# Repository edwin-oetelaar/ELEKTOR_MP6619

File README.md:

# ELEKTOR_MP6619 Breakout Board Project

This repository contains the KiCAD project files for the Elektor Magazine article about the MP6619 H-bridge chip Breakout Board.

## Software Requirement

This project was designed using the latest nightly version of KiCAD. 

### Installation on Ubuntu:

To install the nightly build of KiCAD on Ubuntu, you can use the following commands:

```bash
sudo add-apt-repository ppa:kicad/kicad-dev-nightly
sudo apt update
sudo apt install kicad-nightly
```
### Installation on Windows:
The KiCAD files have also been tested on Windows. To download the nightly builds for Windows, please visit this link. https://downloads.kicad.org/kicad/windows/explore/nightlies

### Project History
The project evolved over time:

* **First Attempt (Dual Chip Breakout Board)**: The initial design of the project was a dual chip breakout board, found in the directory 2HBR_NG.

* **Second Attempt (Single Chip Breakout Board)**: The design was later revised to create a single chip breakout board, found in the directory 2HBR_NG/2HBR_MINIMAL.

To open the project, use the following command in terminal:

```console
user@werkpc:~$ kicad-nightly 2HBR_NG/2HBR_MINIMAL/2HBR_MINIMAL.kicad_pro
```
### Output Files
The 'out1' directory contains the Gerber files used to manufacture the PCB board.

### Support
If you encounter any issues or require further assistance, feel free to create an issue in this repository.

### License
MIT license, no warranties.
The MIT license is a permissive license that is short and easy to understand. It permits users to use, copy, modify, merge, publish, distribute, sublicense, and sell the software and associated documentation files. Here's the general summary:

  * Use: You can use the hardware in any setting, for any purpose, and without needing to pay for it.

  * Copy: You can make as many copies of the hardware as you want, and give them away or sell them.
  * Modify: You can make changes to the hardware, and use the modified hardware. You can also distribute modified copies, or sell hardware based on the modified designs.
  * Merge: You can combine the hardware with other hardware to make something new, and distribute or sell that.
  * Publish: You can share copies of the hardware, or make them publicly available (for example, by posting them online).
  * Distribute: You can give copies of the hardware to other people.
  * Sublicense: You can allow other people to do any of the above with the hardware.
  * Sell: You can sell copies of the hardware.

The above permissions are granted for free, and apply to both the original version of the hardware and to any modified versions that you make.

The license also includes a "disclaimer of warranty" stating that the hardware is provided "as is" without warranty of any kind.

However, please note that any derivative work you create must maintain the original licensing, i.e., the licensing information must always be included in the hardware documentation, design files, etc.

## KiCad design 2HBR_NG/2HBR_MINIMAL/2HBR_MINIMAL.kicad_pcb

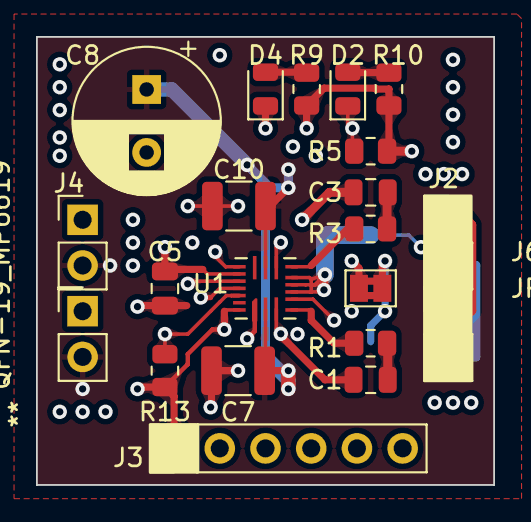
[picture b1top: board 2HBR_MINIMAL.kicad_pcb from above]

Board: 4 copper layers, 25.4 x 24.9 mm, 22 parts (1 on the bottom side), 18 nets.

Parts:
C1, C3: 100 nF / 50V; C_0805_2012Metric
C5: 1uF/50V; C_0805_2012Metric
C7, C10: 4u7 1210; C_1210_3225Metric
C8: 120uF/35; CP_Radial_D8.0mm_P3.50mm
D2: LED RED 0805; LED_0805_2012Metric
D4: LED GREEN 0805; LED_0805_2012Metric
J2, J4, J5, J6: Screw_Terminal_01x02; PinHeader_1x02_P2.54mm_Vertical
J3: Conn_01x06; PinHeader_1x06_P2.54mm_Vertical
JP1: Jumper_2_Bridged; SolderJumper-2_P1.3mm_Bridged2Bar_Pad1.0x1.5mm
R1, R3: 10 R; R_0805_2012Metric
R5: 100k; R_0805_2012Metric
R8: 0.05R SENSE; R_2512_6332Metric
R9: 1K0 0603; R_0805_2012Metric
R10: 1K0 0805; R_0805_2012Metric
R13: 80k 0805; R_0805_2012Metric
U1: QFN-19_MP6619; MP6619GQ-P

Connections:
GND: C7.2, C8.2, C10.2, J4.1, J5.1, JP1.2 (B), R8.2
GNDA: C5.1, D4.1 (K), J3.1, JP1.1 (A), R13.2, U1.19 (AGND)
unnamed: C1.2, R1.2
unnamed: C3.1, R3.1
unnamed: D2.2 (A), R10.2
unnamed: D4.2 (A), R9.2
unnamed: R3.2, U1.9 (BST1)
unnamed: R1.1, U1.4 (BST2)
U1-EN: J3.4, U1.5 (EN)
U1-IFB: R8.1, U1.1 (IFB), U1.6 (LSS), U1.7 (LSS), U1.8 (LSS)
U1-IN1: J3.3, U1.15 (IN1)
U1-IN2: J3.2, U1.16 (IN2)
U1-ISET: R13.1, U1.17 (ISET)
U1-OUT1: C3.2, J2.1, J6.1, U1.10 (OUT1)
U1-OUT2: C1.1, J2.2, J6.2, U1.3 (OUT2)
U1-VCC: C5.2, J3.6, R5.1, R9.1, R10.1, U1.14 (VCC)
U1-nFault: D2.1 (K), J3.5, R5.2, U1.13 (NFAULT)
VIN: C7.1, C8.1, C10.1, J4.2, J5.2, U1.2 (VIN), U1.11 (VIN)

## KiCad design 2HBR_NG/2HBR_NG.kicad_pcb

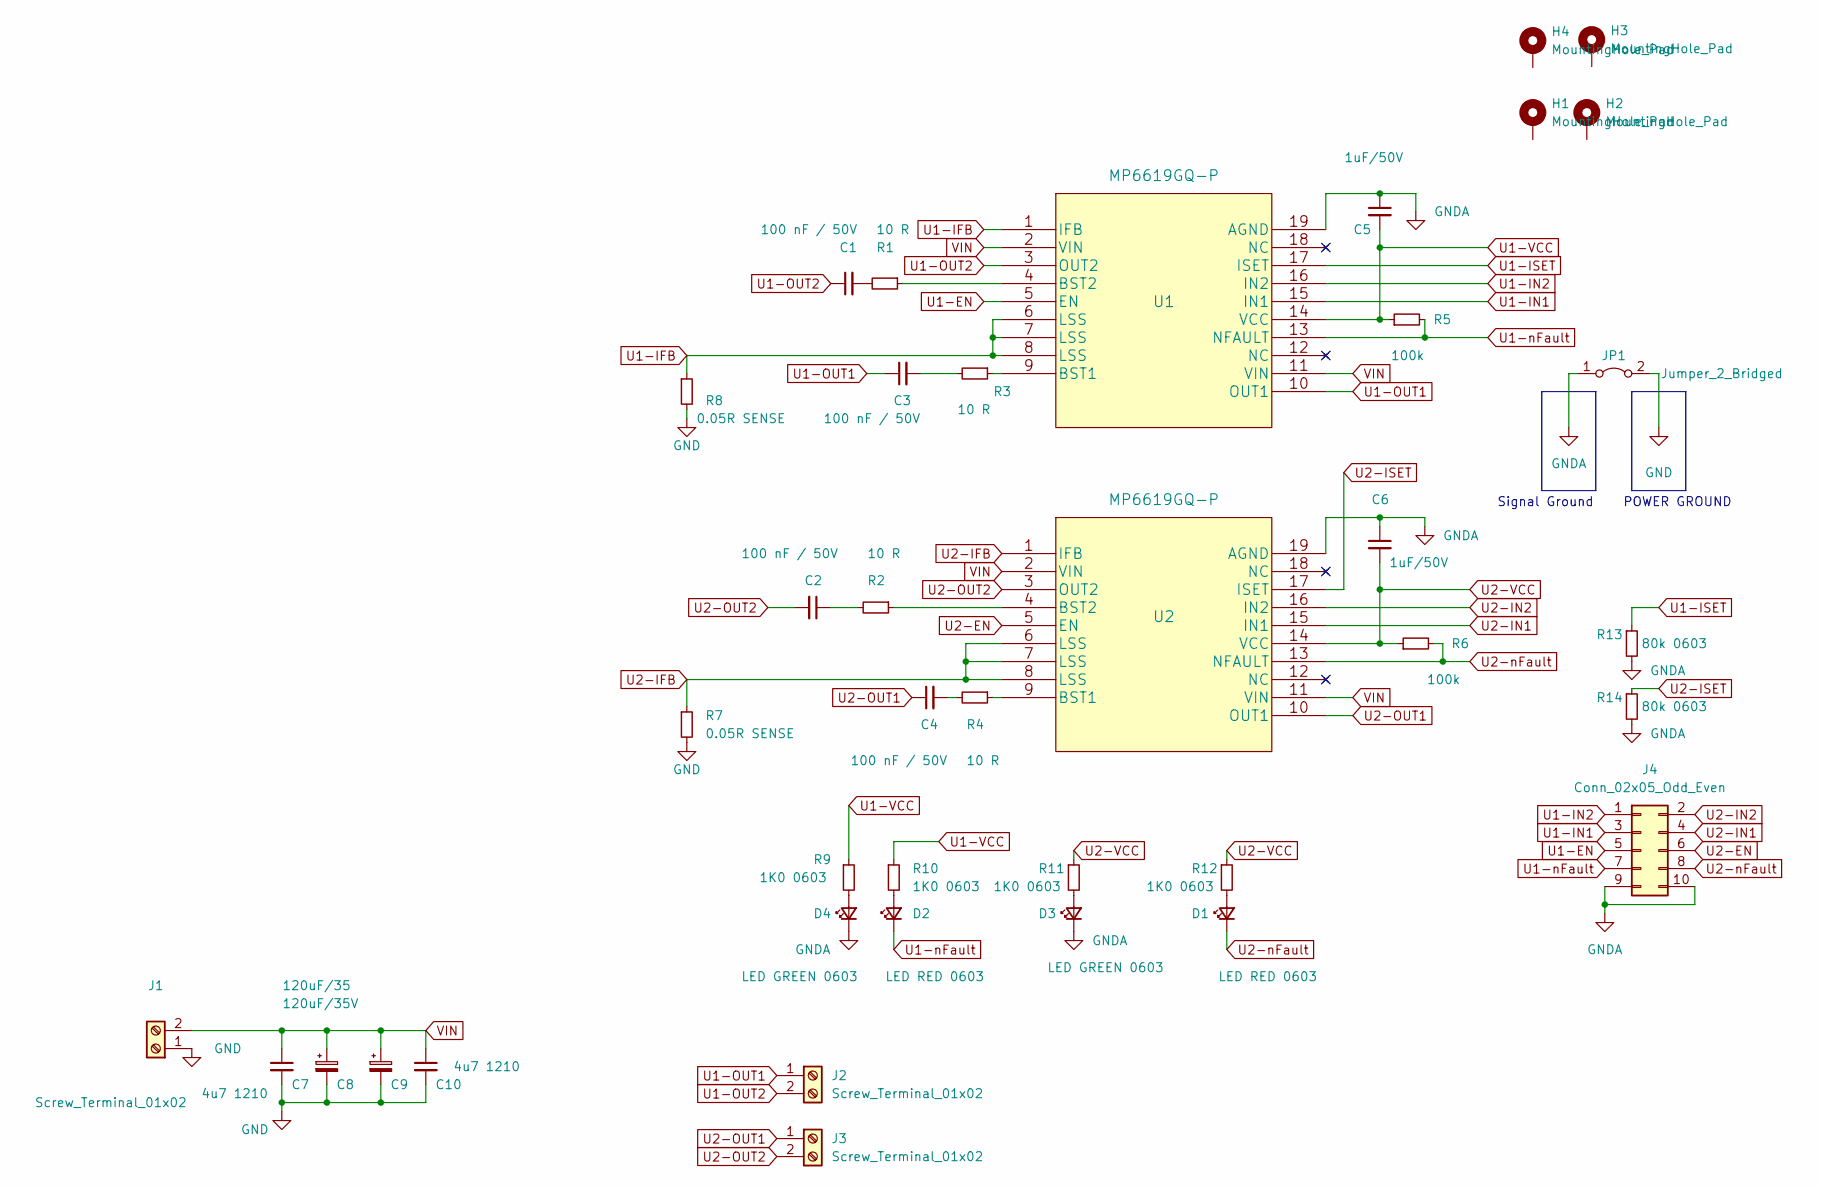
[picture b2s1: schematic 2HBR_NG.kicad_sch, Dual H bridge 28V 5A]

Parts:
C1, C2, C3, C4: 100 nF / 50V; C_0805_2012Metric; PARTNO MC0805B104K500CT
C5, C6: 1uF/50V; C_0805_2012Metric
C7, C10: 4u7 1210; C_1210_3225Metric
C8: 120uF/35; CP_Radial_D8.0mm_P3.50mm
C9: 120uF/35V; CP_Radial_D8.0mm_P3.50mm
D1, D2: LED RED 0603; LED_0603_1608Metric
D3, D4: LED GREEN 0603; LED_0603_1608Metric
H1, H2, H3, H4: MountingHole_Pad; MountingHole_3mm_Pad_Via
J1, J2, J3: Screw_Terminal_01x02; TerminalBlock_bornier-2_P5.08mm
J4: Conn_02x05_Odd_Even; PinHeader_2x05_P2.54mm_Vertical
JP1: Jumper_2_Bridged; SolderJumper-2_P1.3mm_Bridged2Bar_Pad1.0x1.5mm
R1, R2, R3, R4: 10 R; R_0805_2012Metric
R5, R6: 100k; R_0805_2012Metric; PARTNO CR0805-JW-104ELF
R7, R8: 0.05R SENSE; R_2512_6332Metric; PARTNO RL2512FK-070R05L
R9, R10, R11, R12: 1K0 0603; R_0603_1608Metric
R13, R14: 80k 0603; R_0603_1608Metric
U1, U2: MP6619GQ-P

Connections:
GND: C7.2, C8.2, C9.2, C10.2, J1.1, JP1.2 (B), R7.2, R8.2
GNDA: C5.1, C6.1, D3.1 (K), D4.1 (K), J4.9, J4.10, JP1.1 (A), R13.2, R14.2, U1.19 (AGND), U2.19 (AGND)
unnamed: C3.2, R3.2
unnamed: C4.2, R4.2
unnamed: D1.2 (A), R12.2
unnamed: D2.2 (A), R10.2
unnamed: D3.2 (A), R11.2
unnamed: R1.1, U1.4 (BST2)
unnamed: C1.2, R1.2
unnamed: C2.1, R2.2
unnamed: R3.1, U1.9 (BST1)
unnamed: R4.1, U2.9 (BST1)
unnamed: D4.2 (A), R9.2
unnamed: R2.1, U2.4 (BST2)
U1-EN: J4.5, U1.5 (EN)
U1-IFB: R8.1, U1.1 (IFB), U1.6 (LSS), U1.7 (LSS), U1.8 (LSS)
U1-IN1: J4.3, U1.15 (IN1)
U1-IN2: J4.1, U1.16 (IN2)
U1-ISET: R13.1, U1.17 (ISET)
U1-OUT1: C3.1, J2.1, U1.10 (OUT1)
U1-OUT2: C1.1, J2.2, U1.3 (OUT2)
U1-VCC: C5.2, R5.1, R9.1, R10.1, U1.14 (VCC)
U1-nFault: D2.1 (K), J4.7, R5.2, U1.13 (NFAULT)
U2-EN: J4.6, U2.5 (EN)
U2-IFB: R7.1, U2.1 (IFB), U2.6 (LSS), U2.7 (LSS), U2.8 (LSS)
U2-IN1: J4.4, U2.15 (IN1)
U2-IN2: J4.2, U2.16 (IN2)
U2-ISET: R14.1, U2.17 (ISET)
U2-OUT1: C4.1, J3.1, U2.10 (OUT1)
U2-OUT2: C2.2, J3.2, U2.3 (OUT2)
U2-VCC: C6.2, R6.1, R11.1, R12.1, U2.14 (VCC)
U2-nFault: D1.1 (K), J4.8, R6.2, U2.13 (NFAULT)
VIN: C7.1, C8.1, C9.1, C10.1, J1.2, U1.2 (VIN), U1.11 (VIN), U2.2 (VIN), U2.11 (VIN)

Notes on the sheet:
POWER GROUND
Signal Ground

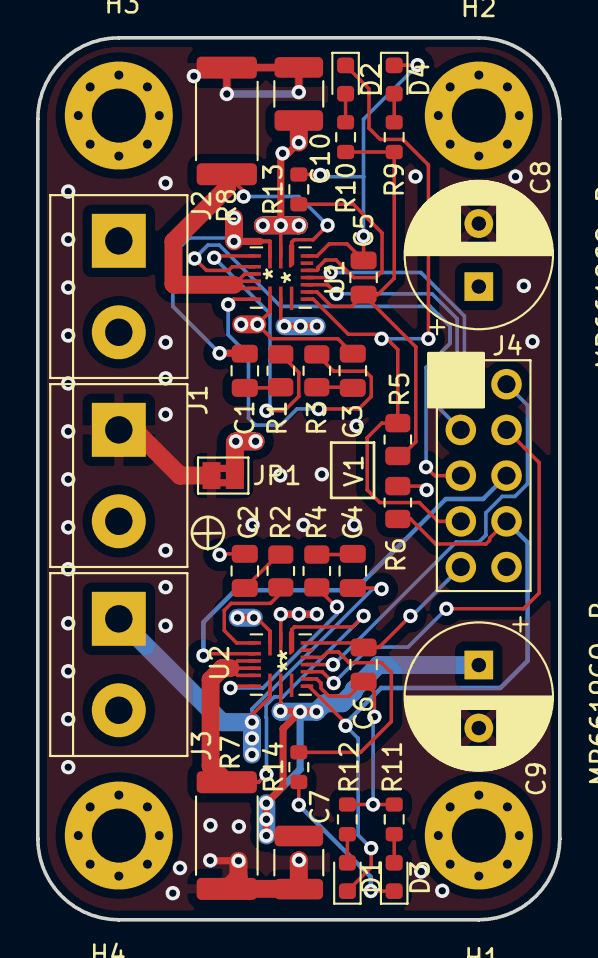
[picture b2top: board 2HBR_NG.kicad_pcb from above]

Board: 4 copper layers, 29.0 x 49.0 mm, 39 parts (0 on the bottom side), 33 nets.

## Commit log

2023-05-21 First commit to public github of Elektor project MP6619
2023-05-21 added pictures to readme
2023-05-23 added the link to windows download nighties

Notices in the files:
parts and their libraries:
All rights reserved.: Cmts.User
Copyright 2021 Accelerated Designs. All rights reserved.
